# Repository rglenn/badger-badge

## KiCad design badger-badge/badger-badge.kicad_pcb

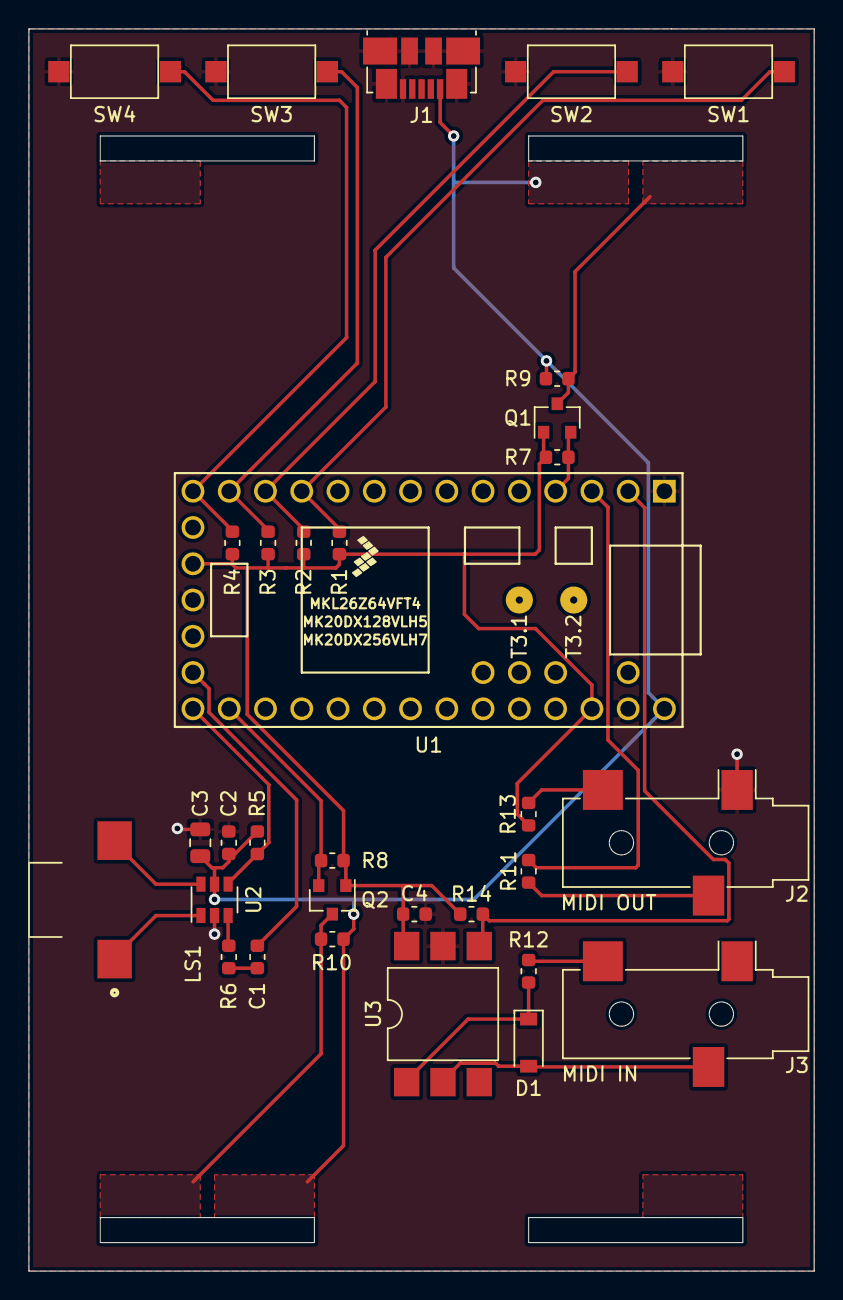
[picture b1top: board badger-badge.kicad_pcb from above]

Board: 2 copper layers, 55.0 x 87.0 mm, 32 parts (0 on the bottom side), 24 nets.

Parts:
C1, C4: 100n; C_0603_1608Metric
C2: 1u; C_0603_1608Metric
C3: 10u; C_0805_2012Metric
D1: 1N4148W; D_SOD-123
J1: USB_B_Micro; USB_Micro-B_Molex_47346-0001
J2, J3: AudioJack3; Jack_3.5mm_CUI_SJ-3523-SMT_Horizontal
LS1: SMT-1127-S-R; XDCR_SMT-1127-S-R
Q1, Q2: BSS138; SOT-23
R1, R2, R3, R4, R5, R7, R8, R9, R10: 4.7K; R_0603_1608Metric
R6: 47K; R_0603_1608Metric
R11, R13: 51; R_0603_1608Metric
R12: 220; R_0603_1608Metric
R14: 470; R_0603_1608Metric
SW1, SW2, SW3, SW4: SW_Push; SW_SPST_CK_RS282G05A3
U1: Teensy3.2; Teensy30_31_32_LC
U2: PAM8301; SOT-23-6
U3: H11L1; SMDIP-6_W9.53mm

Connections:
+3V3: C4.1, Q1.1, Q2.1, R1.2, R2.2, R3.2, R4.2, R7.1, R8.1, R13.1, R14.2, U1.16, U1.31, U3.6
+5V: C2.1, C3.1, J1.1, R5.1, R9.1, R10.1, U1.33, U2.5
/AUDIO: C1.2, U1.19
/BUTTON1: R1.1, SW1.2, U1.11
/BUTTON2: R2.1, SW2.2, U1.12
/BUTTON3: R3.1, SW3.2, U1.13
/BUTTON4: R4.1, SW4.2, U1.14
/MIDI_RX: R14.1, U1.2, U3.4
/MIDI_TX: R11.1, U1.3
/NEOPIXEL1: Q1.2, R7.2, U1.4
/NEOPIXEL1_5V: Q1.3, R9.2
/NEOPIXEL2: Q2.2, R8.2, U1.21
/NEOPIXEL2_5V: Q2.3, R10.2
/~AMP_SD: R5.2, U1.20, U2.4
GND: C2.2, C3.2, C4.2, J1.5, J1.6, J2.S, SW1.1, SW2.1, SW3.1, SW4.1, U1.1, U1.17, U1.32, U2.2, U3.5
unnamed: C1.1, R6.2
unnamed: D1.1, R12.1, U3.1
unnamed: D1.2, J3.R, U3.2
unnamed: J2.R, R11.2
unnamed: J2.T, R13.2
unnamed: J3.T, R12.2
unnamed: LS1.1, U2.1
unnamed: LS1.2, U2.6
unnamed: R6.1, U2.3

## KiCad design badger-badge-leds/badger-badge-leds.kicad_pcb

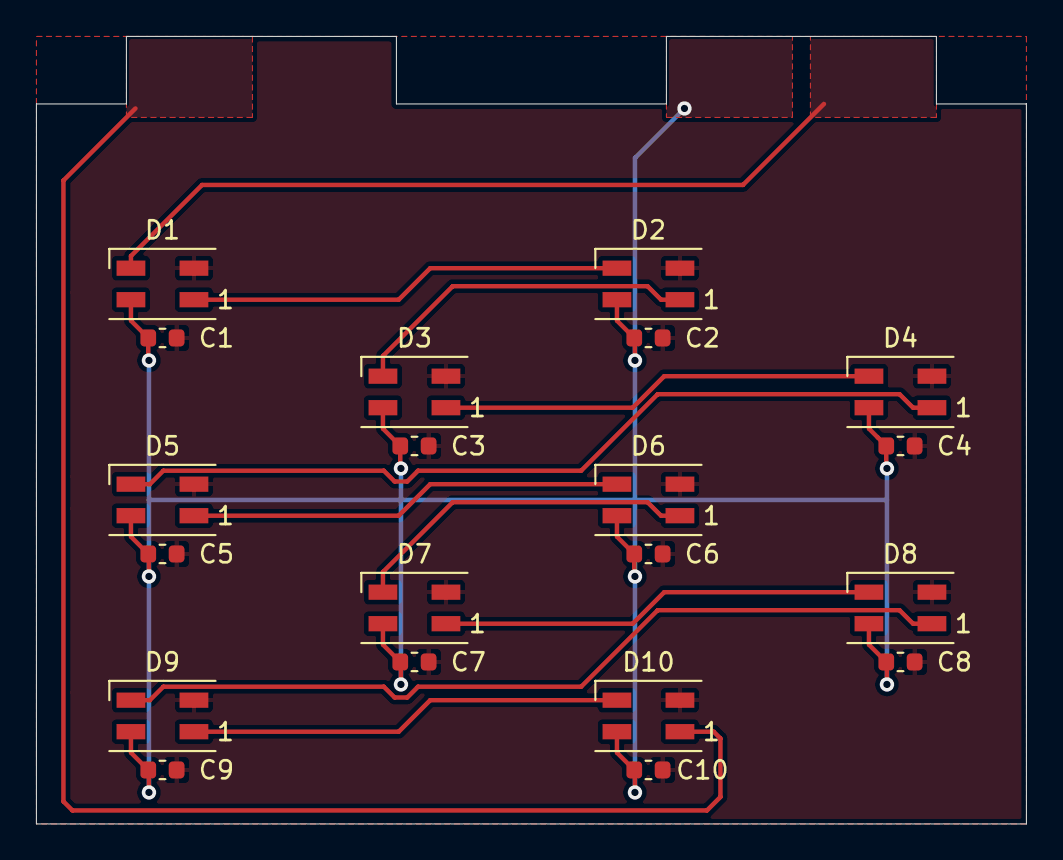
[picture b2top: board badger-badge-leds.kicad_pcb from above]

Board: 2 copper layers, 55.0 x 43.8 mm, 20 parts (0 on the bottom side), 11 nets.

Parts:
C1, C2, C3, C4, C5, C6, C7, C8, C9, C10: 1u; C_0603_1608Metric
D1, D2, D3, D4, D5, D6, D7, D8, D9, D10: SK6812MINI; LED_SK6812MINI_PLCC4_3.5x3.5mm_P1.75mm

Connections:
+5V: C1.1, C2.1, C3.1, C4.1, C5.1, C6.1, C7.1, C8.1, C9.1, C10.1, D1.4, D2.4, D3.4, D4.4, D5.4, D6.4, D7.4, D8.4, D9.4, D10.4
GND: C1.2, C2.2, C3.2, C4.2, C5.2, C6.2, C7.2, C8.2, C9.2, C10.2, D1.2, D2.2, D3.2, D4.2, D5.2, D6.2, D7.2, D8.2, D9.2, D10.2
unnamed: D1.1, D2.3
unnamed: D2.1, D3.3
unnamed: D3.1, D4.3
unnamed: D4.1, D5.3
unnamed: D5.1, D6.3
unnamed: D6.1, D7.3
unnamed: D7.1, D8.3
unnamed: D8.1, D9.3
unnamed: D9.1, D10.3

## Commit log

2019-11-07 Initial import
2019-11-07 Added PDF schematics
2019-11-07 Adding test firmware to exercise neopixels and audio out
2019-11-08 Added defines for buttons
2019-11-15 Adding audio playback code. Currently the distortion level is... significant.
2019-11-16 Updating sound file and header file. Adding timestamps.txt.
2019-11-16 Progress on badger animation structure
2019-11-16 Added timestamps to array
2019-11-17 Merged Erin's code and mine. Buttons do nothing, and I'm not 100% on how in-sync the animation is, but wow, it works!
